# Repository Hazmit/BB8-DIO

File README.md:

# BB8-DIO
BB8 Lights and audio circuit board

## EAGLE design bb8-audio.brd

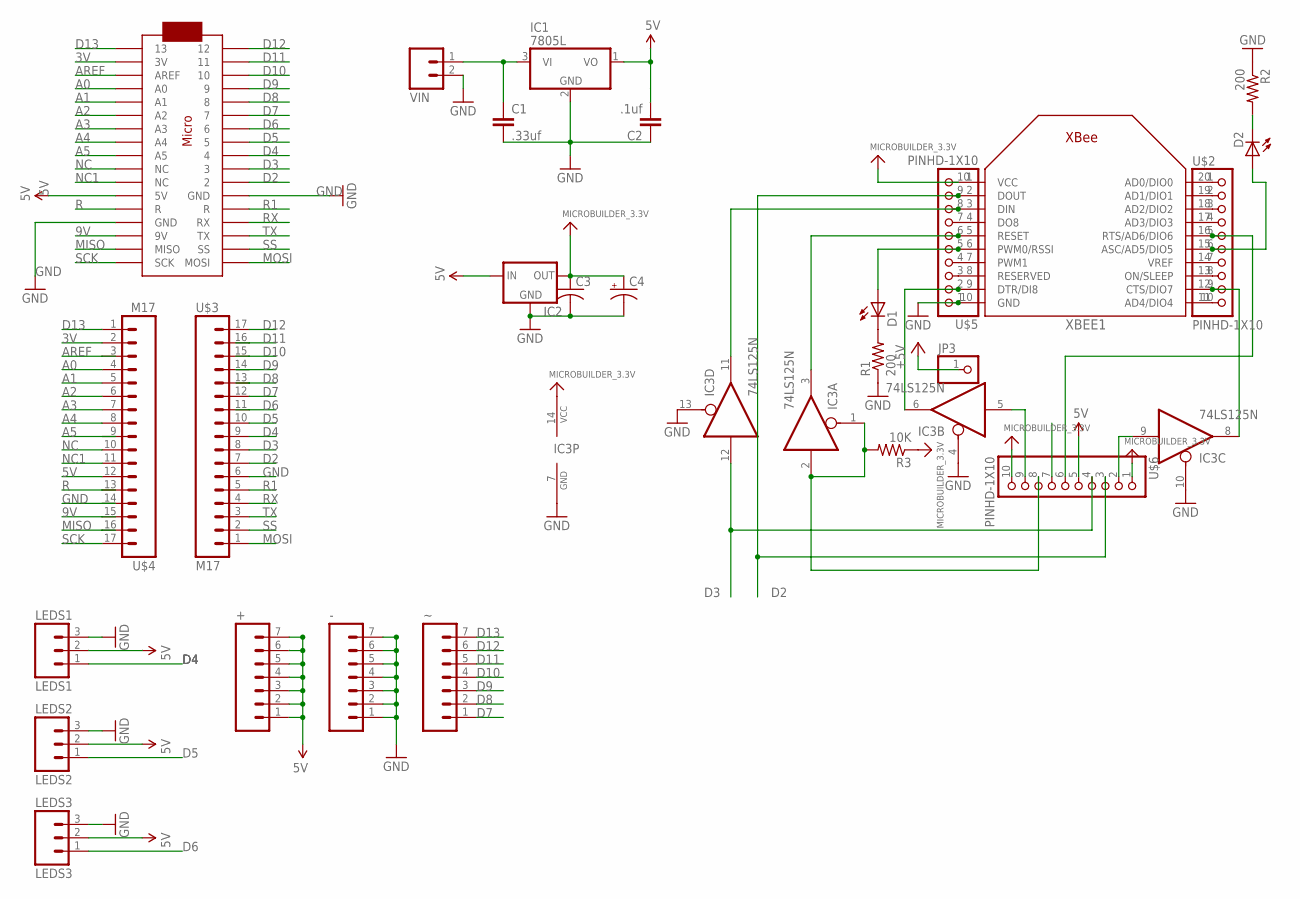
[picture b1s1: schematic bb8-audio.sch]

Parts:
+: M07; 1X07
-: M07; 1X07
C1: .33uf; CAP-PTH-SMALLEZ
C2: .1uf; CAP-PTH-SMALLEZ
C3: C-US025-025X050; C025-025X050
C4: CPOL-USE2.5-5; E2,5-5
D1, D2: LED3MM
IC1: 7805L; TO92
IC2: MC1700; TO92
IC3: 74LS125N; DIL14
JP3: PINHD-1X1; 1X01
LEDS1: LEDS1; 1X03
LEDS2: LEDS2; 1X03
LEDS3: LEDS3; 1X03
R1, R2: 200; 0207/10
R3: 10K; 0207/10
U$1: ARDUINOMICRO
U$2, U$5, U$6: PINHD-1X10; 1X10-BIG
U$3, U$4: M17; 1X17
VIN: M02PTH; 1X02
XBEE1: XBEE
~: M07; 1X07

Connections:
3.3V: C3.1, C4.+, IC2.3 (OUT), IC3.14 (VCC), R3.1, U$5.10, U$6.1, U$6.10, XBEE1.1 (VCC)
3V: U$1.P$33 (3V), U$4.2
5V: +.1, +.2, +.3, +.4, +.5, +.6, +.7, C2.2, IC1.1 (VO), IC2.2 (IN), LEDS1.2, LEDS2.2, LEDS3.2, U$1.P$23 (5V), U$4.12, U$6.5
9V: U$1.P$20 (9V), U$4.15
+5V: JP3.1
A0: U$1.P$31 (A0), U$4.4
A1: U$1.P$30 (A1), U$4.5
A2: U$1.P$29 (A2), U$4.6
A3: U$1.P$28 (A3), U$4.7
A4: U$1.P$27 (A4), U$4.8
A5: U$1.P$26 (A5), U$4.9
AREF: U$1.P$32 (AREF), U$4.3
D2: U$1.P$11 (2), U$3.7, U$5.9, U$6.3, XBEE1.2 (DOUT)
D3: IC3.12 (I), U$1.P$10 (3), U$3.8, U$6.4
D4: LEDS1.1, U$1.P$9 (4), U$3.9
D5: LEDS2.1, U$1.P$8 (5), U$3.10
D6: LEDS3.1, U$1.P$7 (6), U$3.11
D7: U$1.P$6 (7), U$3.12, ~.1
D8: U$1.P$5 (8), U$3.13, ~.2
D9: U$1.P$4 (9), U$3.14, ~.3
D10: U$1.P$3 (10), U$3.15, ~.4
D11: U$1.P$2 (11), U$3.16, ~.5
D12: U$1.P$1 (12), U$3.17, ~.6
D13: U$1.P$34 (13), U$4.1, ~.7
GND: -.1, -.2, -.3, -.4, -.5, -.6, -.7, C1.2, C2.1, C3.2, C4.-, IC1.2 (GND), IC2.1 (GND), IC3.4 (OE), IC3.7 (GND), IC3.10 (OE), IC3.13 (OE), LEDS1.3, LEDS2.3, LEDS3.3, R1.1, R2.1, U$1.P$12 (GND), U$1.P$21 (GND), U$3.6, U$4.14, U$5.1, VIN.2, XBEE1.10 (GND)
MISO: U$1.P$19 (MISO), U$4.16
MOSI: U$1.P$17 (MOSI), U$3.1
unnamed: C1.1, IC1.3 (VI), VIN.1
unnamed: IC3.11 (O), U$5.8, XBEE1.3 (DIN)
unnamed: IC3.8 (O), U$2.9, XBEE1.12 (CTS/DIO7)
unnamed: U$5.7, XBEE1.4 (DO8)
unnamed: D1.A, U$5.5, XBEE1.6 (PWM0/RSSI)
unnamed: D1.K (C), R1.2
unnamed: D2.K (C), R2.2
unnamed: D2.A, U$2.6, XBEE1.15 (ASC/AD5/DIO5)
unnamed: IC3.6 (O), U$5.2, XBEE1.9 (DTR/DI8)
unnamed: U$5.3, XBEE1.8 (RESERVED)
unnamed: U$5.4, XBEE1.7 (PWM1)
unnamed: U$2.1, XBEE1.20 (AD0/DIO0)
unnamed: U$2.2, XBEE1.19 (AD1/DIO1)
unnamed: U$2.3, XBEE1.18 (AD2/DIO2)
unnamed: U$2.4, XBEE1.17 (AD3/DIO3)
unnamed: U$2.7, XBEE1.14 (VREF)
unnamed: U$2.8, XBEE1.13 (ON/SLEEP)
unnamed: U$2.10, XBEE1.11 (AD4/DIO4)
unnamed: IC3.9 (I), U$6.2
unnamed: IC3.3 (O), U$5.6, XBEE1.5 (RESET)
unnamed: IC3.5 (I), U$6.9
NC: U$1.P$25 (NC), U$4.10
NC1: U$1.P$24 (NC), U$4.11
R: U$1.P$13 (R), U$4.13
R1: U$1.P$22 (R), U$3.5
RESET: IC3.1 (OE), IC3.2 (I), R3.2, U$6.8
RTS1: U$2.5, U$6.6, XBEE1.16 (RTS/AD6/DIO6)
RX: U$1.P$14 (RX), U$3.4
SCK: U$1.P$18 (SCK), U$4.17
SS: U$1.P$16 (SS), U$3.2
TX: U$1.P$15 (TX), U$3.3

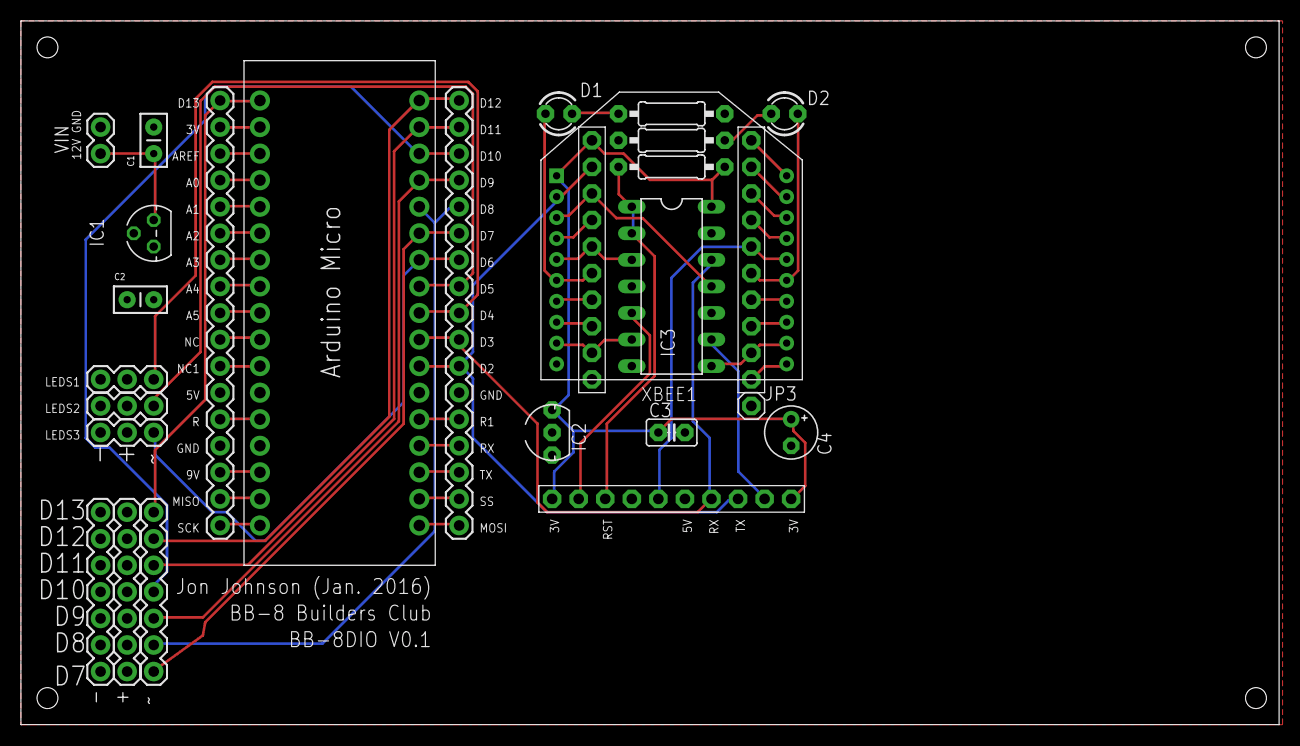
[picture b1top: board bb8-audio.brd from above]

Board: 2 copper layers, 120.3 x 67.3 mm, 27 parts (0 on the bottom side), 57 nets.

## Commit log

2016-02-19 Initial Board Files
    Adding the initial board schematic and pcb files. v0.1
2016-02-19 Updated to use Arduino Pro Mini
    Updated board and schematic to have an arduino pro mini instead of a
    micro.
2016-03-09 BB-8DIO version 3
    Added breakout board to the project for audio breakout. Changed some
    silk screen issues. Swapped positive and neg leads on LED header to
    match neopixel connections. Adding gerber files used for Seed FAB.
    Added a power switch. Fixed issues with VCC 5V and GND on Xbee headers
    and pro mini.

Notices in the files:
parts and their libraries:
SparkFun-Connectors: Licensing: CC v3.0 Share-Alike You are welcome to use this library for commercial purposes.
